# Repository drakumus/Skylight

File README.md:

# About
This is Skylight, a numpad with two rotary encoders using ATMEGA32a-PU Microcontroller.

# Project Details
## case
`case` the files used to laser cut my case out of acrylic and stainless steel. SendCutSend was a responsive and friendly service I used with reasonable prices, so I'd recommend contacting them.

### Files Required for Fabrication:
```
x1	bottom plate (closed).dxf 	- 3mm acrylic
x1	bottom plate (no usb).dxf 	- 3mm acrylic
x2	bottom plate.dxf		- 3mm acrylic
x1	plate.dxf			- stainless steel, ideal 1.5mm
x1	top plate v2.dxf		- 3mm acrylic
```
### Other Files
Other files can either be used for modeling i.e. the base.step which is a 3d render of the pcb for case design, or are previous iterations of files that I kept for future reference.
## USBaspLoader (bootloader)
ATMEGA32A-PU does not come with native USB support. A bootloader with VUSB support must be flashed to let QMK Toolbox recognize the device for flashing via USBasp. This is achieved with USBaspLoader.
I've included my confuration of the loader with instructions to use below.

**NOTE:** Flashing on windows requires avrdude. The sourceforge version of Avrdude that I will not link to **DELETES YOUR PATH ENVIRONMENT VARIABLE**. I did this twice on two different installs of windows before figuring it out. I hope you find a better way to install. You may have better luck with choco package manager for windows but the current version on there is 6.3 which requires custom drivers you must place manually in your system32 folder. The other option is WSL however I believe there are still limitations for that to see COM ports. I hope the future has a more dev friendly approach.
### Requirements
 - ISP (I repurposed a Pro Micro to do this, [see qmk's guide](https://github.com/qmk/qmk_firmware/blob/master/docs/isp_flashing_guide.md))
 - Avrdude
 - Git Bash (other WSL consoles probably work)
### Loading the Bootloader
1. Open [QMK Toolbox](https://github.com/qmk/qmk_toolbox/releases)
2. Check what COM port your ISP is plugged into (i.e. COM3)
3. Edit Makefile.inc (line 41) in the USBaspLoader folder with the correct COM port and the isp specified in the QMK guide above.
		i.e. `PROGRAMMER = -c avrisp -P COM3`
4. `cd` into my version of USBaspLoader with git bashs
5. Use git bash (has make tools we need) to execute:
  	1. make firmware
	2. avrdude -c avrisp -p m32 -P COM6 -v 
		- make sure the device number is not 0x00000, if it is double check the pin configuration on your ISP
	3. avrdude -c avrisp -p m32 -P COM6 -v -u -U lfuse:w:0x1F:m
	4. avrdude -c avrisp -p m32 -P COM6 -v -u -U hfuse:w:0xC0:m
	5. make flash
	6. avrdude -c avrisp -p m32 -P COM6 -U flash:r:-:i
		- this just reads the flash memory space to make sure the bits were set.

Congrats you now have a bootloader installed. You're now ready to flash your first firmware.
## firmware
**NOTE:** Do not attempt to flash the hex from qmk_firmware until after a bootloader has been flashed (found in USBaspLoader).

This folder contains the qmk firmware flashed to the board. Note that I flash the via supported kecap set.
If you want to play with this dump this folder into the keyboard folder in the qmk_firmware repository.
### Example build:
Open QMK MYSYS and run `qmk compile -kb zoci/skylight -km via` after dropping the zoci folder into the qmk_firmware/keyboard folder.
### Flashing the Board
1. In order to flash the two 2.54mm female "jumper" pins towards the right, top side of the board must be connected together. You can do this with tweezers or a wire.
2. Plug in the board via USB-C port on the device to USB-A on your computer.
3. QMK Toolbox should now detect the device (if the bootloader has been flashed previously)
4. Select the `zoci_skylight_via.hex` file in the firmware folder and click Flash.
5. Once it says flash complete disconnect the board from the computer then remove the connection between the two jumper pins.
6. Plug the board back into the computer.

You now have a functioning PCB!
### Via Support
> :warning: **Only use static RGB**: other color modes will cause the board to crash repeatedly forcing a reflash! This is likely because the microcontroller is too slow to continuously write rgb data.

In order for via to work with this board you must:
1. Go to the `SETTINGS` tab and toggle the "Show Design tab" to on.
2. Go to the `DESIGN` tab and select "LOAD" then open the via.json: `./firmware/zoci/skylight_s2/via.json`
3. Go to the `CONFIGURE` tab.
4. You may have to unplug and replug the board for it to show up. In general it is recommended to launch via then plug in the board.

You now can modify the button controls in via instead of building your own qmk hex!

## kicad files

This folder contains the kicad project and its dependancies.
**Note:** You must clone recursively to get the submodule requirements for the kicad dependencies to load properly.
### Files Required for Fabrication
```
./Fabrication Files/plots final.zip
```

You can upload this file to a site like JLCPCB for fabrication.
### BOM
TODO

# Images

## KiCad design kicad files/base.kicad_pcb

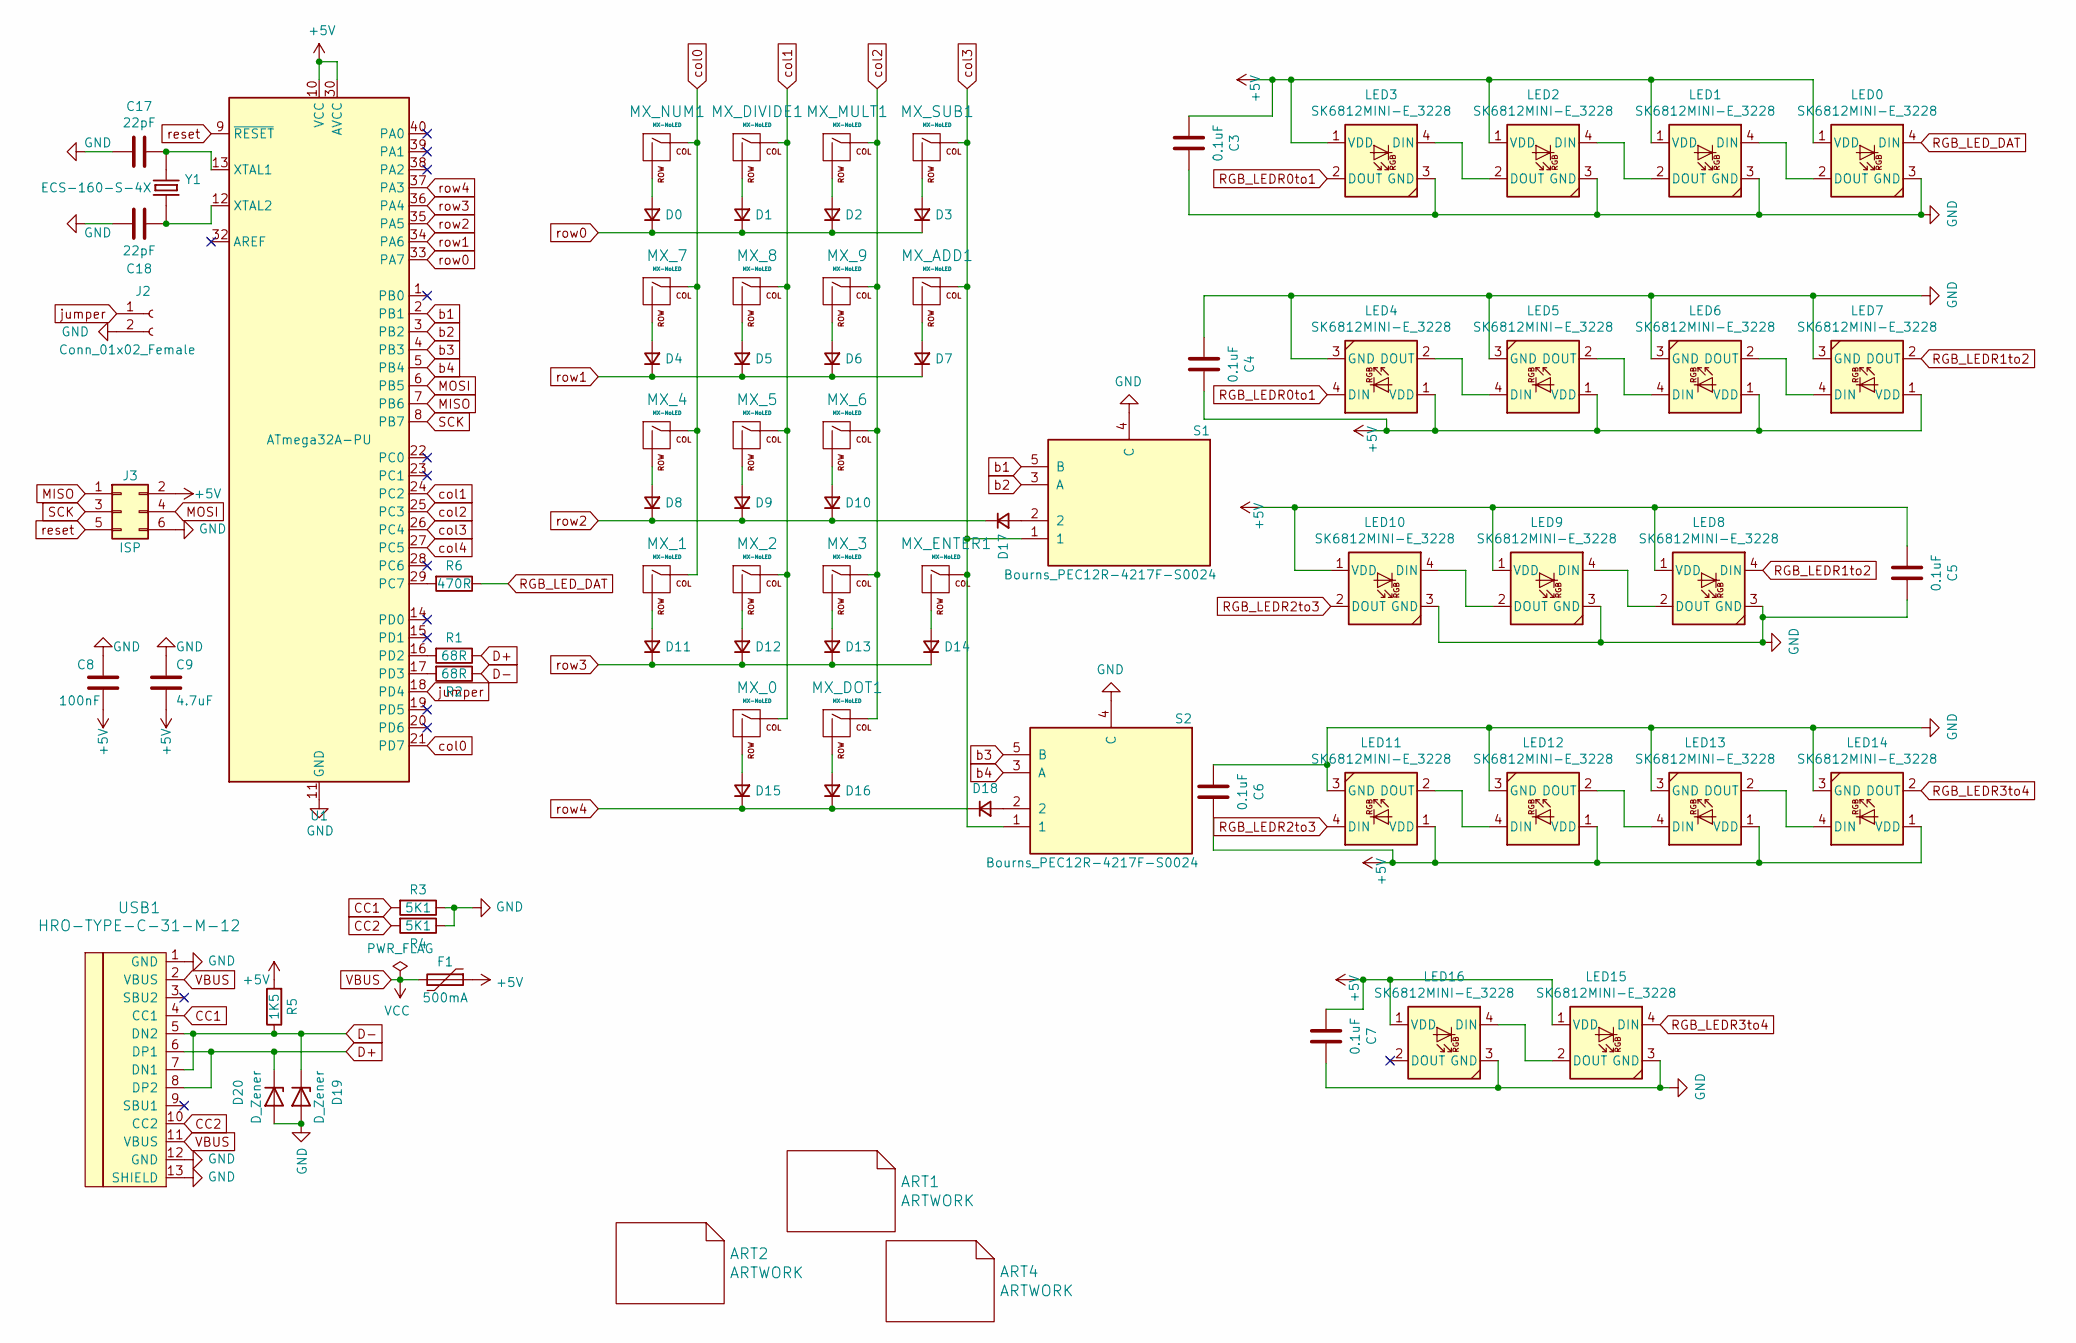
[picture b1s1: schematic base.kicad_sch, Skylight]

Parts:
ART1: ARTWORK; border and silhouette
ART2: ARTWORK; name
ART4: ARTWORK; avenda
C3, C4, C5, C6, C7: 0.1uF; C_Disc_D3.8mm_W2.6mm_P2.50mm
C8: 100nF; C_Disc_D3.8mm_W2.6mm_P2.50mm
C9: 4.7uF; C_Disc_D3.8mm_W2.6mm_P2.50mm
C17, C18: 22pF; C_Disc_D3.8mm_W2.6mm_P2.50mm
D0, D1, D2, D3, D4, D5, D6, D7, D8, D9, D10, D11, D12, D13, D14, D15, D16, D17, D18: D_Small; D_DO-35_SOD27_P7.62mm_Horizontal
D19, D20: D_Zener; D_DO-35_SOD27_P7.62mm_Horizontal
F1: 500mA; Fuse_1206_3216Metric
J2: Conn_01x02_Female; PinHeader_1x02_P2.54mm_Vertical
J3: ISP; PinHeader_2x03_P2.54mm_Vertical
LED0, LED1, LED2, LED3, LED4, LED5, LED6, LED7, LED8, LED9, LED10, LED11, LED12, LED13, LED14, LED15, LED16: SK6812MINI-E_3228; SK6812-MINI-E
MX_0: MX-NoLED; MXOnly-2U-Hotswap
MX_1, MX_2, MX_3, MX_4, MX_5, MX_6, MX_7, MX_8, MX_9: MX-NoLED; MXOnly-1U-Hotswap-Antishear
MX_ADD1: MX-NoLED; MXOnly-2U-Hotswap
MX_DIVIDE1: MX-NoLED; MXOnly-1U-Hotswap-Antishear
MX_DOT1: MX-NoLED; MXOnly-1U-Hotswap-Antishear
MX_ENTER1: MX-NoLED; MXOnly-2U-Hotswap
MX_MULT1: MX-NoLED; MXOnly-1U-Hotswap-Antishear
MX_NUM1: MX-NoLED; MXOnly-1U-Hotswap-Antishear
MX_SUB1: MX-NoLED; MXOnly-1U-Hotswap-Antishear
R1, R2: 68R; R_Axial_DIN0204_L3.6mm_D1.6mm_P7.62mm_Horizontal
R3, R4: 5K1; R_Axial_DIN0204_L3.6mm_D1.6mm_P7.62mm_Horizontal
R5: 1K5; R_Axial_DIN0204_L3.6mm_D1.6mm_P7.62mm_Horizontal
R6: 470R; R_Axial_DIN0204_L3.6mm_D1.6mm_P7.62mm_Horizontal
S1, S2: Bourns_PEC12R-4217F-S0024; PEC12R-4xxF-Sxxxx
U1: ATmega32A-PU; DIP-40_W15.24mm
USB1: HRO-TYPE-C-31-M-12; HRO-TYPE-C-31-M-12-HandSoldering
Y1: ECS-160-S-4X; XTAL_ECS-160-S-4X

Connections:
+5V: C3.2, C4.1, C5.2, C6.1, C7.2, C8.2, C9.2, F1.1, J3.2, LED0.1 (VDD), LED1.1 (VDD), LED2.1 (VDD), LED3.1 (VDD), LED4.1 (VDD), LED5.1 (VDD), LED6.1 (VDD), LED7.1 (VDD), LED8.1 (VDD), LED9.1 (VDD), LED10.1 (VDD), LED11.1 (VDD), LED12.1 (VDD), LED13.1 (VDD), LED14.1 (VDD), LED15.1 (VDD), LED16.1 (VDD), R5.2, U1.10 (VCC), U1.30 (AVCC)
CC1: R3.2, USB1.4 (CC1)
CC2: R4.2, USB1.10 (CC2)
D+: D20.1 (K), R1.1, USB1.6 (DP1), USB1.8 (DP2)
D-: D19.1 (K), R2.1, R5.1, USB1.5 (DN2), USB1.7 (DN1)
GND: C3.1, C4.2, C5.1, C6.2, C7.1, C8.1, C9.1, C17.2, C18.2, D19.2 (A), D20.2 (A), J2.2, J3.6, LED0.3 (GND), LED1.3 (GND), LED2.3 (GND), LED3.3 (GND), LED4.3 (GND), LED5.3 (GND), LED6.3 (GND), LED7.3 (GND), LED8.3 (GND), LED9.3 (GND), LED10.3 (GND), LED11.3 (GND), LED12.3 (GND), LED13.3 (GND), LED14.3 (GND), LED15.3 (GND), LED16.3 (GND), R3.1, R4.1, S1.4 (C), S2.4 (C), U1.11 (GND), U1.31 (GND), USB1.1 (GND), USB1.12 (GND), USB1.13 (SHIELD)
MISO: J3.1, U1.7 (PB6)
MOSI: J3.4, U1.6 (PB5)
unnamed: C17.1, U1.13 (XTAL1), Y1.1
unnamed: C18.1, U1.12 (XTAL2), Y1.2
unnamed: D0.2 (A), MX_NUM1.2 (ROW)
unnamed: D1.2 (A), MX_DIVIDE1.2 (ROW)
unnamed: D2.2 (A), MX_MULT1.2 (ROW)
unnamed: D3.2 (A), MX_SUB1.2 (ROW)
unnamed: D4.2 (A), MX_7.2 (ROW)
unnamed: D5.2 (A), MX_8.2 (ROW)
unnamed: D6.2 (A), MX_9.2 (ROW)
unnamed: D7.2 (A), MX_ADD1.2 (ROW)
unnamed: D8.2 (A), MX_4.2 (ROW)
unnamed: D9.2 (A), MX_5.2 (ROW)
unnamed: D10.2 (A), MX_6.2 (ROW)
unnamed: D11.2 (A), MX_1.2 (ROW)
unnamed: D12.2 (A), MX_2.2 (ROW)
unnamed: D13.2 (A), MX_3.2 (ROW)
unnamed: D14.2 (A), MX_ENTER1.2 (ROW)
unnamed: D15.2 (A), MX_0.2 (ROW)
unnamed: D16.2 (A), MX_DOT1.2 (ROW)
unnamed: D17.2 (A), S1.2
unnamed: D18.2 (A), S2.2
unnamed: LED0.2 (DOUT), LED1.4 (DIN)
unnamed: LED1.2 (DOUT), LED2.4 (DIN)
unnamed: LED2.2 (DOUT), LED3.4 (DIN)
unnamed: LED4.2 (DOUT), LED5.4 (DIN)
unnamed: LED5.2 (DOUT), LED6.4 (DIN)
unnamed: LED6.2 (DOUT), LED7.4 (DIN)
unnamed: LED8.2 (DOUT), LED9.4 (DIN)
unnamed: LED9.2 (DOUT), LED10.4 (DIN)
unnamed: LED11.2 (DOUT), LED12.4 (DIN)
unnamed: LED12.2 (DOUT), LED13.4 (DIN)
unnamed: LED13.2 (DOUT), LED14.4 (DIN)
unnamed: LED15.2 (DOUT), LED16.4 (DIN)
unnamed: R1.2, U1.16 (PD2)
unnamed: R2.2, U1.17 (PD3)
unnamed: R6.2, U1.29 (PC7)
RGB_LEDR0to1: LED3.2 (DOUT), LED4.4 (DIN)
RGB_LEDR1to2: LED7.2 (DOUT), LED8.4 (DIN)
RGB_LEDR2to3: LED10.2 (DOUT), LED11.4 (DIN)
RGB_LEDR3to4: LED14.2 (DOUT), LED15.4 (DIN)
RGB_LED_DAT: LED0.4 (DIN), R6.1
SCK: J3.3, U1.8 (PB7)
VBUS: F1.2, USB1.2 (VBUS), USB1.11 (VBUS)
b1: S1.5 (B), U1.2 (PB1)
b2: S1.3 (A), U1.3 (PB2)
b3: S2.5 (B), U1.4 (PB3)
b4: S2.3 (A), U1.5 (PB4)
col0: MX_1.1 (COL), MX_4.1 (COL), MX_7.1 (COL), MX_NUM1.1 (COL), U1.21 (PD7)
col1: MX_0.1 (COL), MX_2.1 (COL), MX_5.1 (COL), MX_8.1 (COL), MX_DIVIDE1.1 (COL), U1.24 (PC2)
col2: MX_3.1 (COL), MX_6.1 (COL), MX_9.1 (COL), MX_DOT1.1 (COL), MX_MULT1.1 (COL), U1.25 (PC3)
col3: MX_ADD1.1 (COL), MX_ENTER1.1 (COL), MX_SUB1.1 (COL), S1.1, S2.1, U1.26 (PC4)
col4: U1.27 (PC5)
jumper: J2.1, U1.18 (PD4)
reset: J3.5, U1.9 (~RESET)
row0: D0.1 (K), D1.1 (K), D2.1 (K), D3.1 (K), U1.33 (PA7)
row1: D4.1 (K), D5.1 (K), D6.1 (K), D7.1 (K), U1.34 (PA6)
row2: D8.1 (K), D9.1 (K), D10.1 (K), D17.1 (K), U1.35 (PA5)
row3: D11.1 (K), D12.1 (K), D13.1 (K), D14.1 (K), U1.36 (PA4)
row4: D15.1 (K), D16.1 (K), D18.1 (K), U1.37 (PA3)

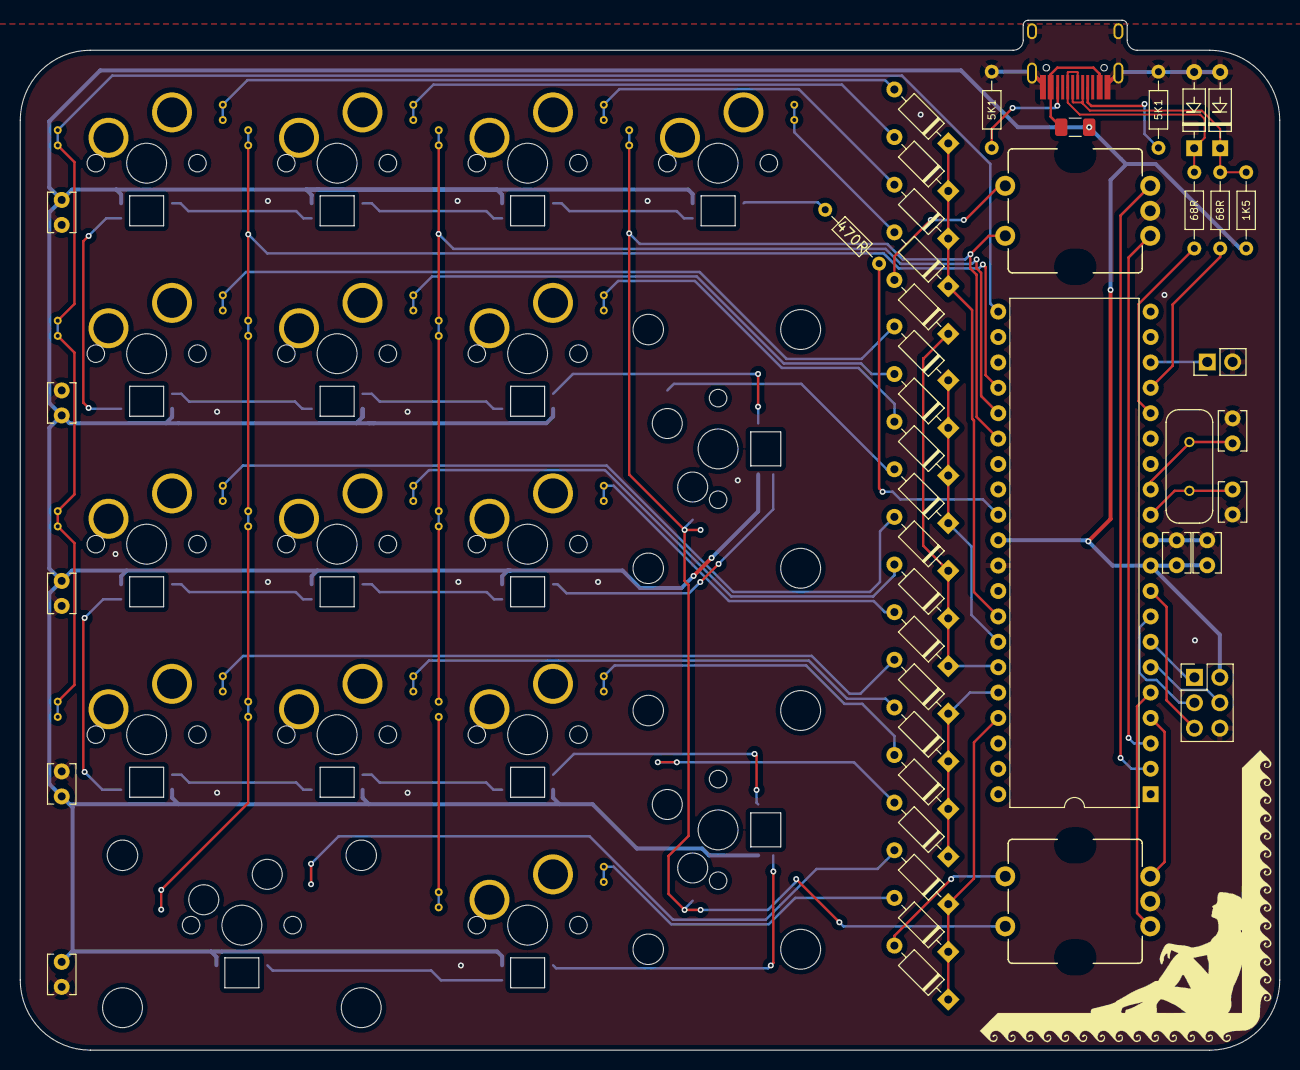
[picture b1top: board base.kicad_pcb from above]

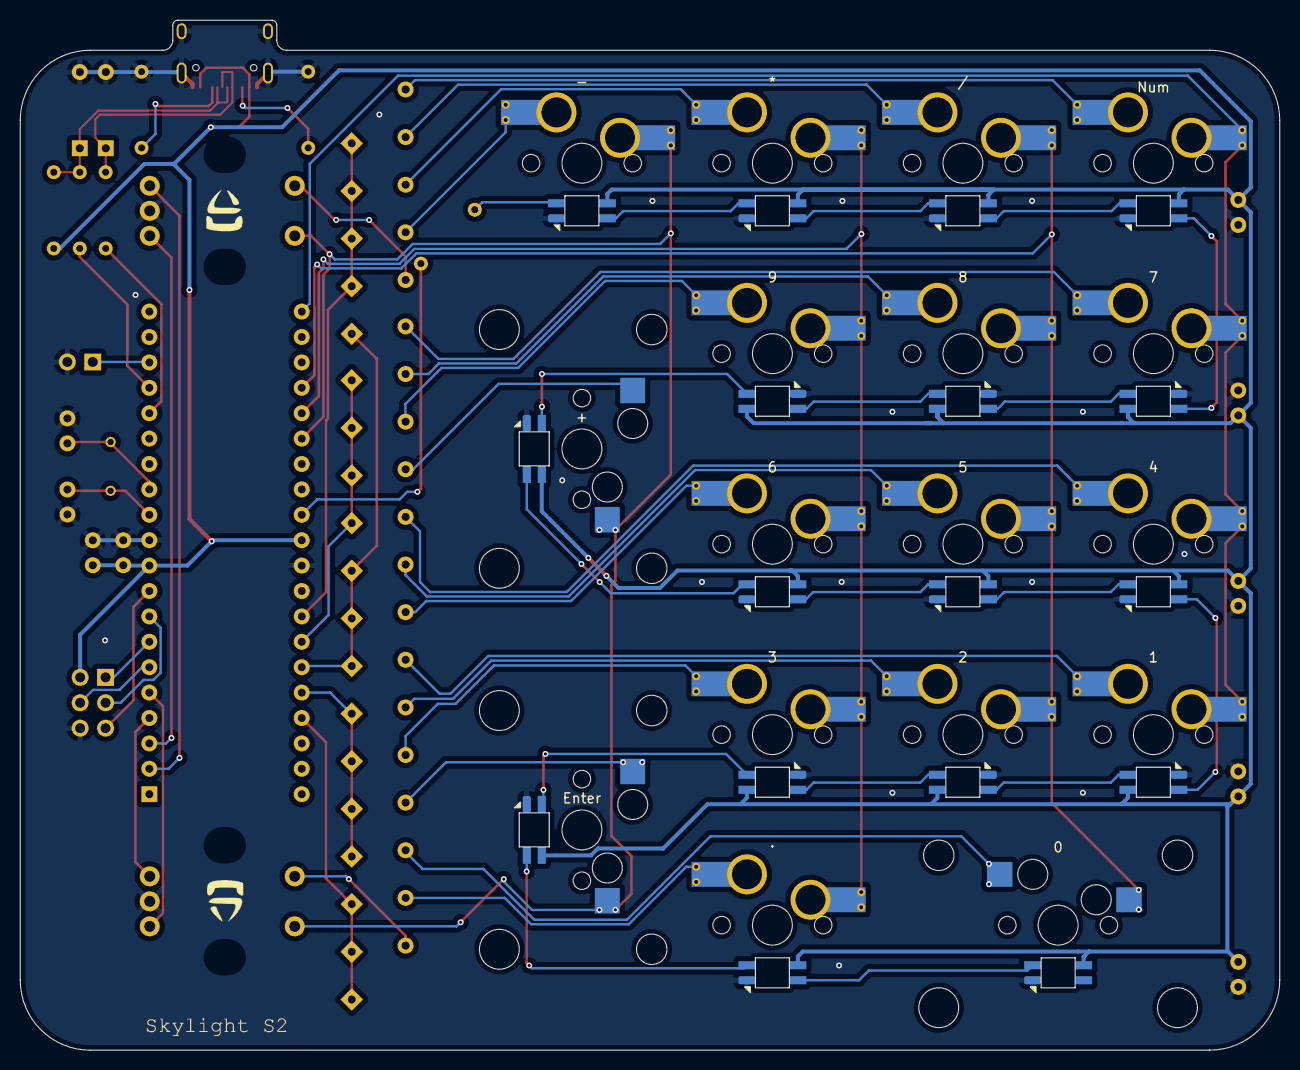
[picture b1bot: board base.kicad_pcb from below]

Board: 2 copper layers, 125.9 x 102.9 mm, 82 parts (20 on the bottom side), 66 nets.

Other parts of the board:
ART4#2: ARTWORK; avenda

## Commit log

2022-06-01 Add photos and via support
2022-06-02 Add Readme
2022-06-02 add kicad-library-win as submodule
2022-06-02 More readme updates
